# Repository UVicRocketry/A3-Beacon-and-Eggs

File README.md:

# A3 Beacon and Eggs

Hardware design files (KiCad 9) for the A3 recovery beacon — a VHF transmitter
stitched to the main recovery shock chord.

## Boards

### `Beacon_and_eggs/` — V1 (fabricated)

40 × 80 mm, 4-layer (F.Cu / GND / PWR / B.Cu).

- **MCU** — STM32F411CEU6 with 25 MHz and 32.768 kHz crystals, SWD header,
  boot/reset circuits, and test points
- **Radio** — SA868S / SA818V VHF module, UART control at 9600 baud, with
  TX_EN and TX_PWR_DN control lines and a TX audio input
- **Sensor** — ADXL343 accelerometer on I²C (ALT ADDRESS tied high → 0x1D)
- **Power** — BQ24070 Li-ion charger, USB-C input with ESD clamps, MIC5528
  3.3 V LDO, NTA4151P / NTA4153N load switches, and a divider for battery
  voltage monitoring on the ADC
- **Antenna** — plated mounting holes serve as the RF feed and ground clamp
  for a fabric antenna. 
- Status LEDs, battery connector, and an interactive BOM under `bom/`

### `Beacon_and_eggs_V2/` — in progress

A condensed second revision. Planned:

- Moved to low frequency LoRa Module with Semtech's SX1278
- Move to a smaller Battery
- PIC MCU to interface with transmitter

WIP

### `Beacon BNC Adapter PCB/`

Two-connector coax breakout, used to attach a standard antenna or analyzer to
the beacon's bare antenna pads for bench testing.

## Firmware

Lives in the separate [A3_Beacon_and_Eggs_FW](https://github.com/zgsdlv/A3_Beacon_and_Eggs_FW)
repository (STM32CubeMX + HAL). It is bring-up code only, written to check that
the V1 hardware works - it reads the accelerometer's ID register, handshakes
with the SA868S, and blinks out which of the two responded.

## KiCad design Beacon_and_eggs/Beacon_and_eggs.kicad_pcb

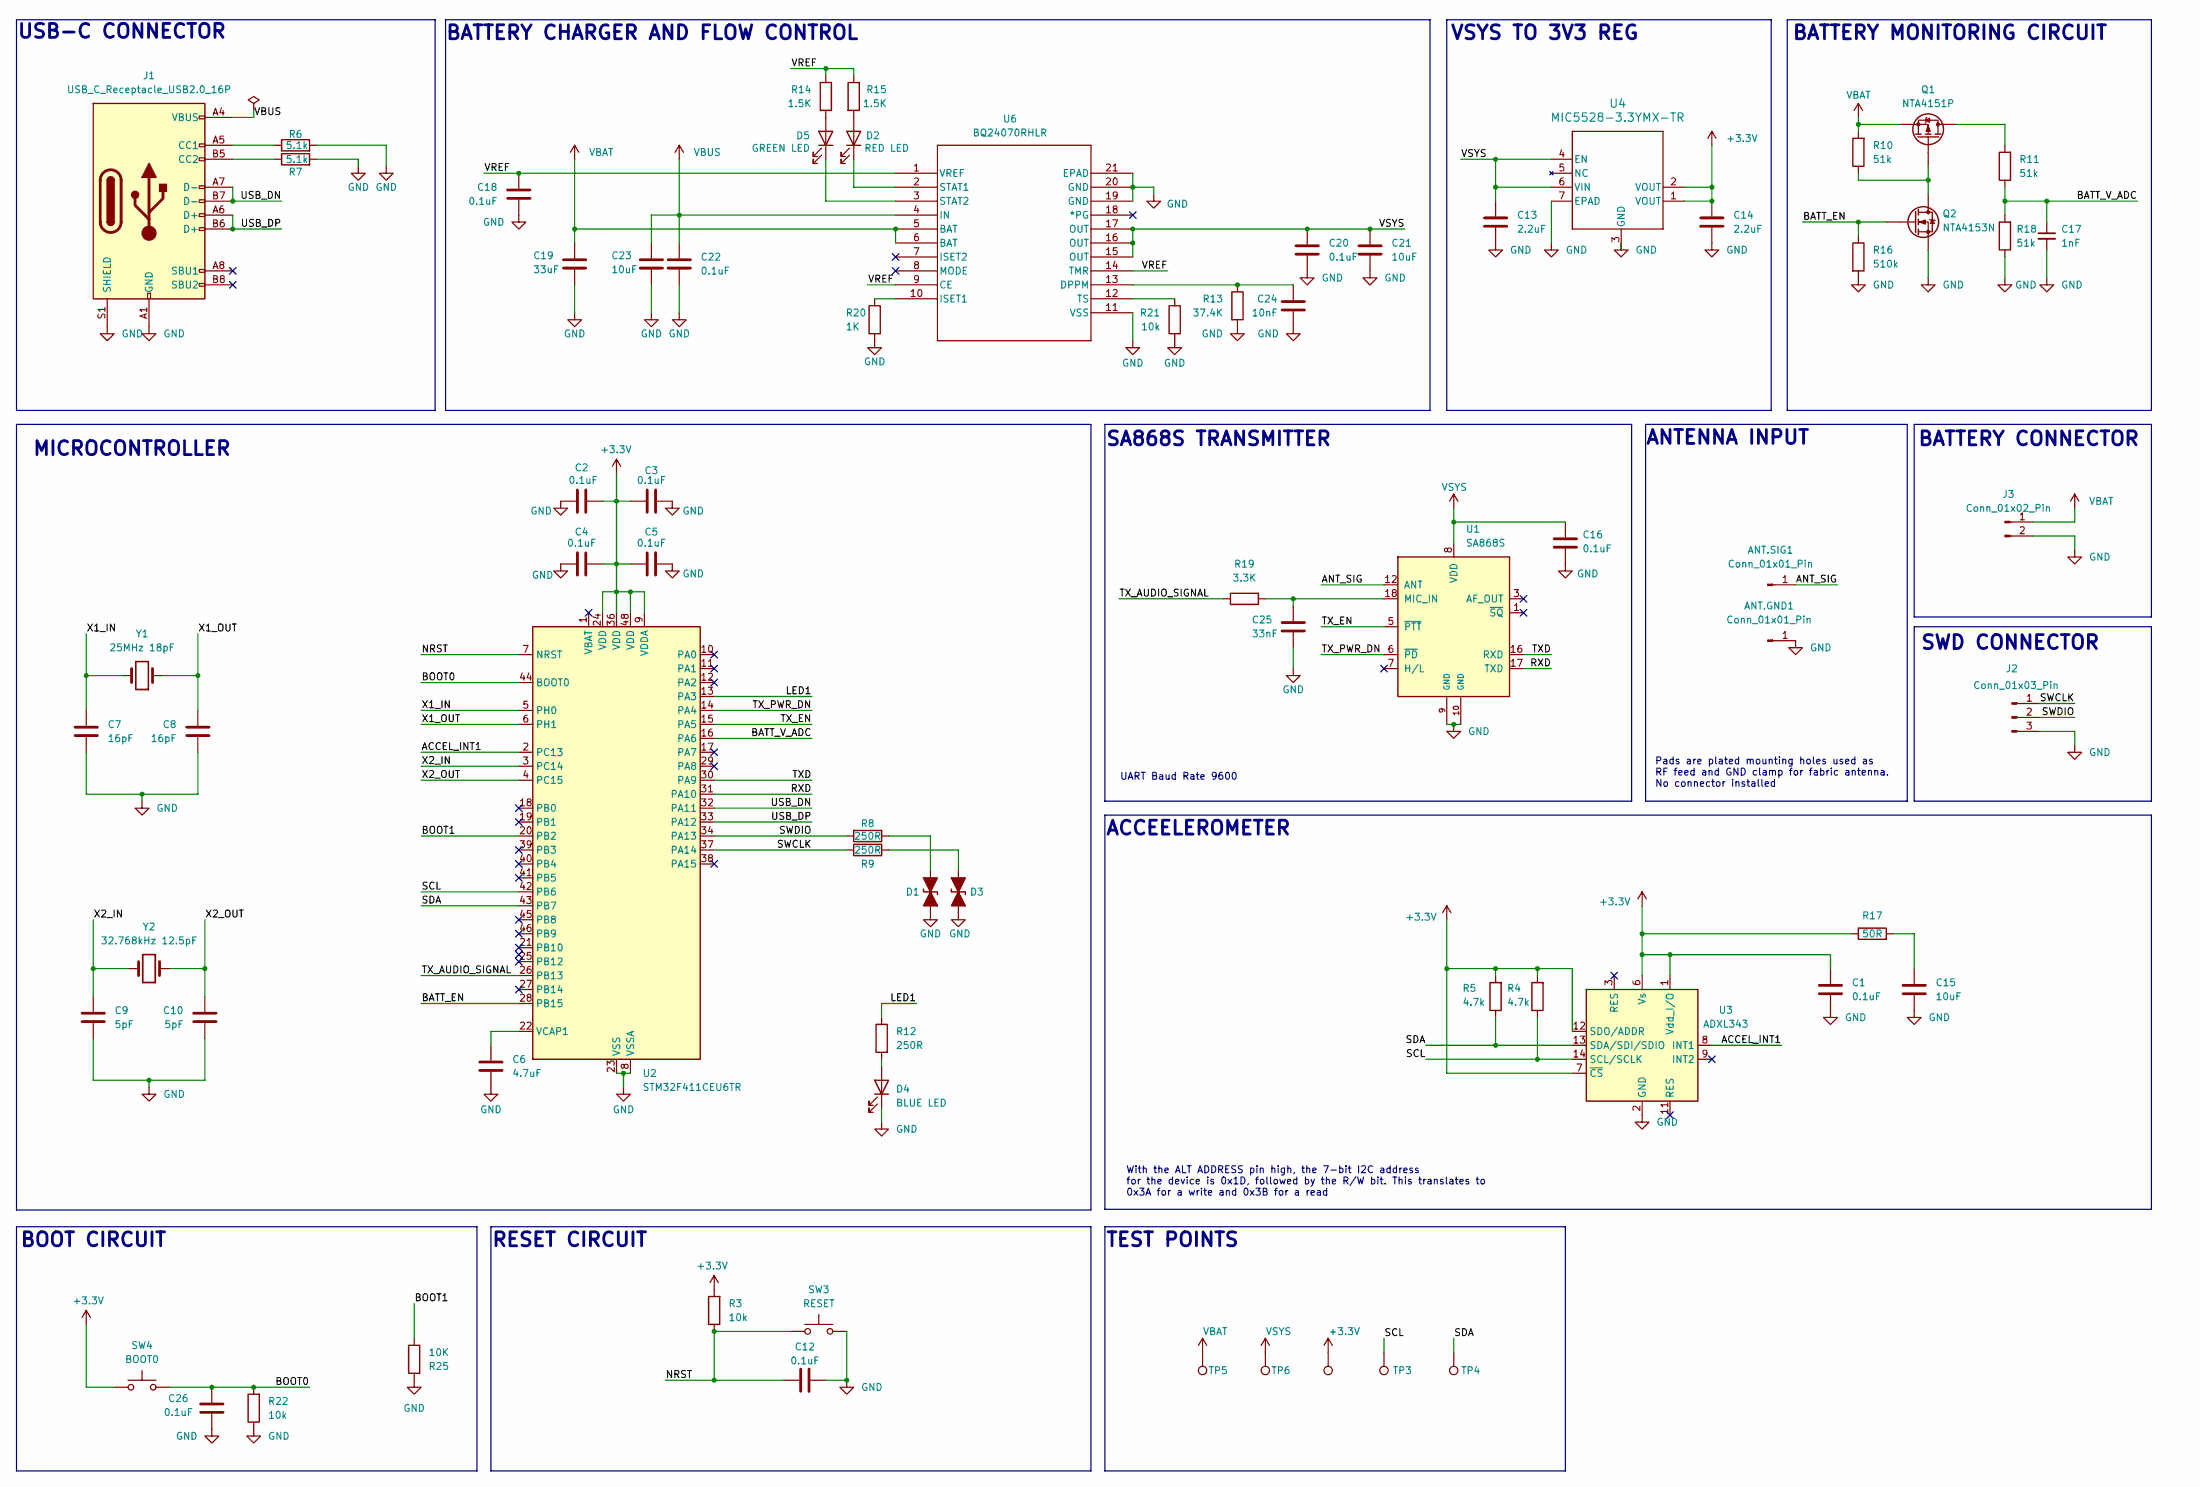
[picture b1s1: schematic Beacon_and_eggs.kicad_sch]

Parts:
3V3: 3V3; TestPoint_THTPad_D1.5mm_Drill0.7mm
ANT.GND1, ANT.SIG1: Conn_01x01_Pin; MountingHole_3.2mm_M3_DIN965_Pad_TopBottom
C1, C12, C16, C18, C20, C22, C26: 0.1uF; C_0402_1005Metric; DigiKey_Part_Number C0402C104K4RACTU
C2, C3, C4, C5: 0.1uF; C_0201_0603Metric; DigiKey_Part_Number GRM033C71C104KE14D
C6: 4.7uF; C_0201_0603Metric; DigiKey_Part_Number GRM035R60J475ME15J
C7, C8: 16pF; C_0402_1005Metric; DigiKey_Part_Number GJM1555C1H160FB01J
C9, C10: 5pF; C_0402_1005Metric; DigiKey_Part_Number GRM1555C1H5R0BA01D
C13, C14: 2.2uF; C_0402_1005Metric; DigiKey_Part_Number GRM155C80J225KE95D
C15, C21, C23: 10uF; C_0402_1005Metric; DigiKey_Part_Number GRM155R61A106ME11D
C17: 1nF; C_0402_1005Metric; Digikey Part Number 1292-1621-1-ND
C19: 33uF; C_0402_1005Metric; DigiKey_Part_Number GRM155R60J156ME15D
C24: 10nF; C_0402_1005Metric; DigiKey_Part_Number GRM155R71C103KA01D
C25: 33nF; C_0402_1005Metric; DigiKey_Part_Number C0402C333J4RACTU
D1, D3: UCLAMP3311P.TCT; D_0402_1005Metric; Manufacturer Part Number UCLAMP3311P.TCT; Digikey Part Number UCLAMP3311PCT-ND
D2: RED LED; LED_0402_1005Metric; DigiKey_Part_Number SML-D12U1WT86
D4: BLUE LED; LED_0805_2012Metric; DigiKey_Part_Number 150080BS75000
D5: GREEN LED; LED_0402_1005Metric; DigiKey_Part_Number 150060GS75000
J1: USB_C_Receptacle_USB2.0_16P; USB_C_Receptacle_GCT_USB4105-xx-A_16P_TopMnt_Horizontal; DigiKey_Part_Number USB4215-03-A
J2: Conn_01x03_Pin; PinHeader_1x03_P2.54mm_Vertical
J3: Conn_01x02_Pin; JST_XH_S2B-XH-A_1x02_P2.50mm_Horizontal
Q1: NTA4151P; SOT50P160X90-3N; Manufacturer Part Number NTA4151PT1G; Digikey Part Number NTA4151PT1GOSCT-ND
Q2: NTA4153N; SOT50P160X90-3N; Manufacturer Part Number NTA4153NT1G; Digikey Part Number NTA4153NT1GOSCT-ND
R3, R21, R22: 10k; R_0402_1005Metric; DigiKey_Part_Number RMCF0402FT10K0
R4, R5: 4.7k; R_0402_1005Metric; DigiKey_Part_Number RC0402JR-074K7L
R6, R7: 5.1k; R_0402_1005Metric; DigiKey_Part_Number RC0402FR-075K1L
R8, R9, R12: 250R; R_0402_1005Metric; DigiKey_Part_Number RE0402BRE07250RL
R10, R11, R18: 51k; R_0402_1005Metric; Digikey Part Number 311-51.0KMCT-ND
R13: 37.4K; R_0402_1005Metric; DigiKey_Part_Number ERJ-2RKF3742X
R14, R15: 1.5K; R_0402_1005Metric; DigiKey_Part_Number RC0402FR-071K5L
R16: 510k; R_0402_1005Metric; Digikey Part Number YAG2713CT-ND
R17: 50R; R_0402_1005Metric; DigiKey_Part_Number RT0402BRE0750RL
R19: 3.3K; R_0402_1005Metric; DigiKey_Part_Number ERA-2AEB332X
R20: 1K; R_0402_1005Metric; DigiKey_Part_Number RC0402FR-071KL
R25: 10K; R_0402_1005Metric; DigiKey_Part_Number RMCF0402FT10K0
SW3: RESET; SW_SPST_PTS810; DigiKey_Part_Number PTS810SJK250SMTR LFS
SW4: BOOT0; SW_SPST_PTS810; DigiKey_Part_Number PTS810SJK250SMTR LFS
TP3: SCL; TestPoint_THTPad_D1.5mm_Drill0.7mm
TP4: SDA; TestPoint_THTPad_D1.5mm_Drill0.7mm
TP5: VBAT; TestPoint_THTPad_D1.5mm_Drill0.7mm
TP6: VSYS; TestPoint_THTPad_D1.5mm_Drill0.7mm
U1: SA868S; VHF_UHF_Module_generic; DigiKey_Part_Number SA868S
U2: STM32F411CEU6TR; QFN-48-1EP_7x7mm_P0.5mm_EP5.6x5.6mm; DigiKey_Part_Number STM32F411CEU6TR
U3: ADXL343; LGA-14_3x5mm_P0.8mm_LayoutBorder1x6y; DigiKey_Part_Number ADXL343BCCZ-RL7
U4: MIC5528-3.3YMX-TR; XTDFN6_1P2X1P2_MCH; DigiKey_Part_Number MIC5528-3.3YMX-TR
U6: BQ24070RHLR; RHL20_2P05X3P05; PARTREV 4219071/A 05/2017; DigiKey_Part_Number 296-19652-1-ND
Y1: 25MHz 18pF; Crystal_SMD_Abracon_ABM8G-4Pin_3.2x2.5mm; DigiKey_Part_Number ABM3-25.000MHZ-D2Y-T
Y2: 32.768kHz 12.5pF; Crystal_SMD_EuroQuartz_EQ161-2Pin_3.2x1.5mm; DigiKey_Part_Number 12.87167

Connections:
+3.3V: 3V3.1 (1_1), C1.1, C2.2, C3.1, C4.2, C5.1, C14.1, R3.2, R4.2, R5.2, R17.1, SW4.3 (B), SW4.4 (B), U2.9 (VDDA), U2.24 (VDD), U2.36 (VDD), U2.48 (VDD), U3.1 (Vdd_I/O), U3.6 (Vs), U3.7 (~CS), U3.12 (SDO/ADDR), U4.1 (VOUT), U4.2 (VOUT)
/ACCEL_INT1: U2.2 (PC13), U3.8 (INT1)
/ANT_SIG: ANT.SIG1.1 (Pin_1_1), U1.12 (ANT)
/BATT_EN: Q2.1 (G), R16.1, U2.28 (PB15)
/BATT_V_ADC: C17.1, R11.1, R18.2, U2.16 (PA6)
/BOOT0: C26.1, R22.2, SW4.1 (A), SW4.2 (A), U2.44 (BOOT0); also elsewhere on the board
/BOOT1: R25.2, U2.20 (PB2)
/LED1: R12.1, U2.13 (PA3)
/NRST: C12.1, R3.1, SW3.1 (A), SW3.2 (A), U2.7 (NRST); also elsewhere on the board
/RXD: U1.17 (TXD), U2.31 (PA10)
/SCL: R4.1, TP3.1 (1_1), U2.42 (PB6), U3.14 (SCL/SCLK)
/SDA: R5.1, TP4.1 (1_1), U2.43 (PB7), U3.13 (SDA/SDI/SDIO)
/SWCLK: J2.1, R9.1, U2.37 (PA14)
/SWDIO: J2.2, R8.2, U2.34 (PA13)
/TXD: U1.16 (RXD), U2.30 (PA9)
/TX_AUDIO_SIGNAL: R19.1, U2.26 (PB13)
/TX_EN: U1.5 (~PTT), U2.15 (PA5)
/TX_PWR_DN: U1.6 (~PD), U2.14 (PA4)
/USB_DN: J1.A7 (D-), J1.B7 (D-), U2.32 (PA11)
/USB_DP: J1.A6 (D+), J1.B6 (D+), U2.33 (PA12)
/VREF: C18.1, R14.1, R15.1, U6.1 (VREF), U6.9 (CE), U6.14 (TMR)
/X1_IN: C7.2, U2.5 (PH0), Y1.2
/X1_OUT: C8.2, U2.6 (PH1), Y1.1
/X2_IN: C9.2, U2.3 (PC14), Y2.2
/X2_OUT: C10.2, U2.4 (PC15), Y2.1
GND: ANT.GND1.1 (Pin_1_1), C1.2, C2.1, C3.2, C4.1, C5.2, C6.1, C7.1, C8.1, C9.1, C10.1, C12.2, C13.2, C14.2, C15.2, C16.2, C17.2, C18.2, C19.2, C20.2, C21.2, C22.2, C23.2, C24.2, C25.2, C26.2, D1.1 (A1), D3.1 (A1), D4.1 (K), J1.A1 (GND), J1.A12 (GND), J1.B1 (GND), J1.B12 (GND), J1.S1 (SHIELD), J1.SH, J2.3, J3.2, Q2.2 (S), R6.2, R7.2, R13.2, R16.2, R18.1, R20.2, R21.2, R22.1, R25.1, SW3.3 (B), SW3.4 (B), U1.9 (GND), U1.10 (GND), U2.8 (VSSA), U2.23 (VSS), U2.35 (VSS), U2.47 (VSS), U2.49 (VSS), U3.2 (GND), U3.4 (GND), U3.5 (GND), U4.3 (GND), U4.7 (EPAD), U6.11 (VSS), U6.19 (GND), U6.20 (GND), U6.21 (EPAD), U6.V
unnamed: C15.1, R17.2
unnamed: D1.2 (A2), R8.1
unnamed: D2.2 (A), R15.2
unnamed: D2.1 (K), U6.2 (STAT1)
unnamed: D3.2 (A2), R9.2
unnamed: D4.2 (A), R12.2
unnamed: D5.2 (A), R14.2
unnamed: D5.1 (K), U6.3 (STAT2)
unnamed: J1.A5 (CC1), R6.1
unnamed: J1.B5 (CC2), R7.1
unnamed: Q1.3 (D1), Q1.8 (D1), R11.2
unnamed: Q1.1 (G1), Q2.3 (D), R10.1
unnamed: C25.1, R19.2, U1.18 (MIC_IN)
unnamed: C6.2, U2.22 (VCAP1)
unnamed: C24.1, R13.1, U6.13 (DPPM)
unnamed: R20.1, U6.10 (ISET1)
unnamed: R21.1, U6.12 (TS)
VBAT: C19.1, J3.1, Q1.2 (S1), R10.2, TP5.1 (1_1), U6.5 (BAT), U6.6 (BAT)
VBUS: C22.1, C23.1, J1.A4 (VBUS), J1.A9 (VBUS), J1.B4 (VBUS), J1.B9 (VBUS), U6.4 (IN)
VSYS: C13.1, C16.1, C20.1, C21.1, TP6.1 (1_1), U1.8 (VDD), U4.4 (EN), U4.6 (VIN), U6.15 (OUT), U6.16 (OUT), U6.17 (OUT)

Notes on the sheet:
BATTERY CONNECTOR
SWD CONNECTOR
RESET CIRCUIT
BOOT CIRCUIT
TEST POINTS
VSYS TO 3V3 REG
SA868S TRANSMITTER
With the ALT ADDRESS pin high, the 7-bit I2C address for the device is 0x1D, followed by the R/W bit. This translates to 0x3A for a write and 0x3B for a read
BATTERY CHARGER AND FLOW CONTROL
USB-C CONNECTOR
Pads are plated mounting holes used as RF feed and GND clamp for fabric antenna. No connector installed
UART Baud Rate 9600
ACCEELEROMETER
ANTENNA INPUT
BATTERY MONITORING CIRCUIT
MICROCONTROLLER

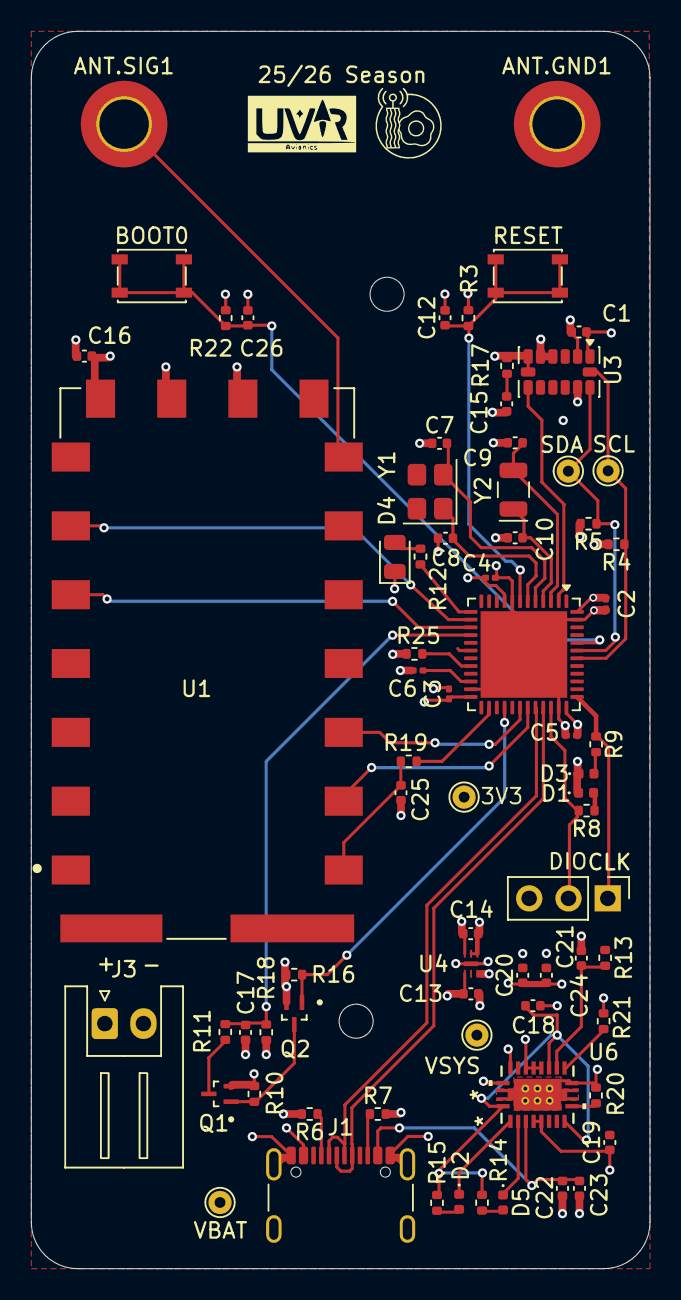
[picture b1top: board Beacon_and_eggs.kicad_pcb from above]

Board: 4 copper layers, 40.0 x 80.0 mm, 72 parts (0 on the bottom side), 46 nets.

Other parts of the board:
BOOT0: BOOT0; SW_SPST_PTS810
RESET: RESET; SW_SPST_PTS810

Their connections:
/BOOT0: BOOT0.1 (A), BOOT0.2 (A); also elsewhere on the board
/NRST: RESET.1 (A), RESET.2 (A); also elsewhere on the board

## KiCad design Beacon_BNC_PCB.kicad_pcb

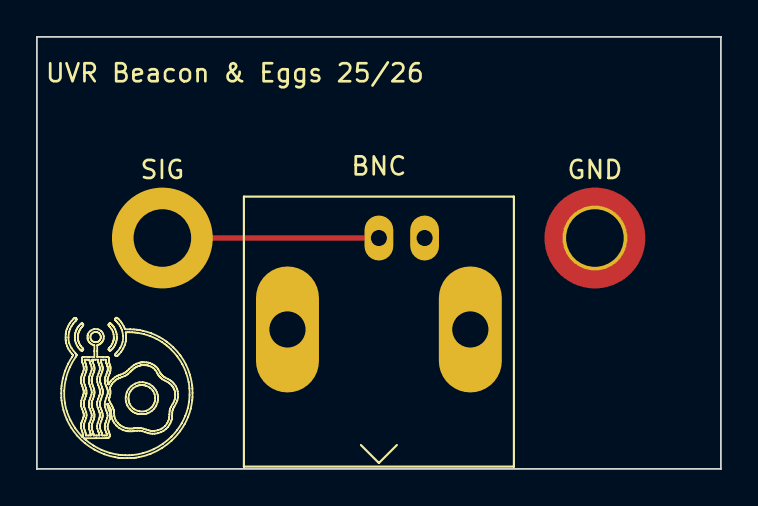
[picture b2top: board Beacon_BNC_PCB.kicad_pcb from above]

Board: 2 copper layers, 38.0 x 24.0 mm, 3 parts (0 on the bottom side), 2 nets.

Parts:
BNC: Conn_Coaxial; BNC_Amphenol_B6252HB-NPP3G-50_Horizontal
GND: MountingHole_3.2mm_M3_DIN965_Pad_TopBottom
SIG: MountingHole_3.2mm_M3_DIN965_Pad_TopBottom

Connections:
/GND: BNC.2 (Ext), GND.1
/RF_IN: BNC.1 (In), SIG.1

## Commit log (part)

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2025-10-26 initial commit, adding BNC Adapter PCBfolder.
2025-10-26 added folder
2025-10-28 increased trace width to .36 and added gerber files
2025-11-25 Uploading KiCAD files
    Yeet
2025-11-26 Reorganization
    Whoot (reorganized the placement of the newly added voltage circuitry, SA868, and ADXL343)
2026-01-13 Reformatted Schematic Layout
    cool beans
2026-01-14 Implemented new boost/buck converter
2026-01-14 Buzzer, USB, and Documentation
    Added the buzzer and USB c circuits, alongside adding boxes with labels to the remaining parts of the circuit
2026-01-14 relabeled some global tags
2026-01-15 Assingned most components(1206 for resistors and Capacitors)
2026-01-15 Organized components to be placed tomorrow
2026-01-15 Started layout process, still needs tracing..
2026-01-15 Revert "Organized components to be placed tomorrow"
    This reverts commit c4bd26fadb75ae4865d41ebab2e9036565b38f13.
2026-01-15 Revert "Assingned most components(1206 for resistors and Capacitors)"
    This reverts commit 7557e7a7bd89896b141ef55f24d0591e6209fe46.
2026-01-16 resolved merge issue
2026-01-16 Laid traces and changed 3.3V regulator
2026-02-09 cheanged schematic and V1 pcb layout completed.
2026-02-10 narrowed the pcb down from 60mm to 40 mm
2026-02-10 added missing via net labels
2026-05-07 Added complete BOM, replaced a footprint, added missing STEP files
2026-05-09 edited silkscreen text
2026-05-14 fixed accel. pinouts, added 10k resistor to TS of U6
2026-05-15 added step file for enclosure design
2026-05-16 reduce drc error to 0, updated step file
2026-05-16 changed batery connector footprint from vert. to horz.
2026-05-19 updated step file
2026-05-20 updated step file, added 3D components
2026-05-20 changed UART software pins to hardware pins, fixed I2C pins
2026-05-27 labelled switches
2026-05-28 added manufacturing files
2026-05-28 Update .gitignore to remove output file entries
    Removed output file patterns from .gitignore
2026-05-28 reattempting to add manufacturing files
2026-05-28 file clean up
2026-06-19 Updated two digipart numbers and remade BOM
